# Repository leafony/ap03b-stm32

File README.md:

# Leafony AP03B STM32

**本ボード（AP03B STM32 リーフ）は、AP03 STM32 リーフと回路図が同一で、互換性があります。**

STM32L452REI6を搭載した、Leafony AP03B STM32リーフのハードウェア設計リポジトリです。KiCadの回路図・PCBレイアウト、面付け基板のGerber・ドリルデータ、専用ライブラリ、部品表（BOM）を収録しています。

設計を開く場合は [KiCadプロジェクト](./kicad/ap03b-stm32/ap03b-stm32.kicad_pro)、部品を確認する場合は [BOM](./docs/leafony-ap03b-stm32-bom.csv) から参照してください。

## ハードウェア概要

| 項目 | 内容 |
| --- | --- |
| MCU | STMicroelectronics STM32L452REI6（U1） |
| CPU | Arm Cortex-M4、FPU搭載、最大80 MHz |
| メモリ | Flash 512 KB / SRAM 160 KB |
| MCUパッケージ | UFBGA-64、5 × 5 mm、0.5 mmピッチ |
| 低速外部クロック | 32.768 kHz水晶（X1） |
| 電源 | Leafonyバスの3.3 V / GND |
| バス接点 | CN1、表裏各29接点 |
| 主なバス信号 | D0〜D13、A0〜A5、SDA / SCL、SWDIO / SWCLK、RESET、AREF |
| 操作・表示 | BOOT0切り替えスイッチ、リセットスイッチ、BOOT0状態表示LED |
| 基板 | 20 × 20 mm、6層、板厚0.8 mm（PCB設計値） |
| 設計リビジョン | v1.0、2026-11-07（単体基板・回路図のタイトル欄） |

CPU・メモリの仕様は [STMicroelectronicsの製品情報](https://www.st.com/en/microcontrollers-microprocessors/stm32l452re.html)、実装部品と接続は本リポジトリの回路図・PCB・BOMを参照しています。最大クロックはMCUの仕様値で、実際の動作クロックはファームウェアの設定によります。

CN1のVBUS端子は未接続で、AREFの接続用抵抗R5は未実装（DNP）です。各端子の接続は [Leafonyバス回路図](./kicad/ap03b-stm32/leafony_bus.kicad_sch) と [MCU回路図](./kicad/ap03b-stm32/stm32.kicad_sch) で確認できます。

### スイッチとLED

| 部品 | 型番 | 回路上の役割 |
| --- | --- | --- |
| SW1（PG） | CUS-12TB | BOOT0のHigh / Lowを切り替える |
| SW2（RST） | EVQ-P7B01P | 押すとRESETをGNDへ接続する |
| D1 | SML-A12U8TT86 | BOOT0がHighのときに点灯する |

詳細は [リセット・プログラム切り替え回路](./kicad/ap03b-stm32/reset_prog.kicad_sch) を参照してください。

## リポジトリ構成

| パス | 内容 |
| --- | --- |
| [kicad/ap03b-stm32/ap03b-stm32.kicad_pro](./kicad/ap03b-stm32/ap03b-stm32.kicad_pro) | 単体基板のKiCadプロジェクト |
| [kicad/ap03b-stm32/ap03b-stm32.kicad_sch](./kicad/ap03b-stm32/ap03b-stm32.kicad_sch) | トップレベル回路図。以下の3シートをまとめる |
| [kicad/ap03b-stm32/stm32.kicad_sch](./kicad/ap03b-stm32/stm32.kicad_sch) | MCU、電源、クロック周辺回路 |
| [kicad/ap03b-stm32/leafony_bus.kicad_sch](./kicad/ap03b-stm32/leafony_bus.kicad_sch) | Leafonyバス接点と信号接続 |
| [kicad/ap03b-stm32/reset_prog.kicad_sch](./kicad/ap03b-stm32/reset_prog.kicad_sch) | リセット、BOOT0切り替え、LED、信号切り替え回路 |
| [kicad/ap03b-stm32/ap03b-stm32.kicad_pcb](./kicad/ap03b-stm32/ap03b-stm32.kicad_pcb) | 単体基板のPCBレイアウト |
| [kicad/ap03b-stm32/panelized/](./kicad/ap03b-stm32/panelized/) | 面付け基板のプロジェクト・PCBレイアウト |
| [kicad/ap03b-stm32/panelized/Gerber/](./kicad/ap03b-stm32/panelized/Gerber/) | 面付け基板のGerber・ドリルデータ |
| [kicad/ap03b-stm32/lib/](./kicad/ap03b-stm32/lib/) | Leafony専用シンボル、フットプリント、3Dモデル配置先 |
| [docs/leafony-ap03b-stm32-bom.csv](./docs/leafony-ap03b-stm32-bom.csv) | 部品表（CSV） |
| [examples/](./examples/) | サンプルコード用ディレクトリ。現時点ではコード未収録 |

KiCadプロジェクト名は `ap03b-stm32` で、設計ファイルは `kicad/ap03b-stm32/` にまとめています。

## KiCadで開く

回路図とPCBは **KiCad 10.0** で保存されています。KiCad 10.0形式を読み込める環境と、KiCad標準のシンボル・フットプリントライブラリを用意してください。

1. リポジトリを取得します。

   ```sh
   git clone https://github.com/leafony/ap03b-stm32.git
   cd ap03b-stm32
   ```

2. KiCadで `kicad/ap03b-stm32/ap03b-stm32.kicad_pro` を開きます。
3. プロジェクト内の `.kicad_sch` を開くと回路図、`.kicad_pcb` を開くと基板レイアウトを確認できます。
4. 回路図のトップシートから「STM32 MCU」「Leafony Bus」「Reset Prog」の各階層シートへ移動します。

専用ライブラリは [sym-lib-table](./kicad/ap03b-stm32/sym-lib-table) と [fp-lib-table](./kicad/ap03b-stm32/fp-lib-table) に登録済みです。どちらも `${KIPRJMOD}/lib/` を参照するため、`kicad/ap03b-stm32/` 以下のディレクトリ構成を保って開いてください。

### 面付け基板について

`kicad/ap03b-stm32/panelized/` に面付け基板のプロジェクトとPCB、同ディレクトリの `Gerber/` にGerber・ドリルデータを収録しています。

面付けPCBのタイトル欄は「Leafony AP03 STM32 / 2025-07-06」で、単体基板の「Leafony AP03B STM32 / 2026-11-07」と異なります。製造に使用する場合は、単体基板の変更が面付けPCBとGerber・ドリルデータに反映されているか確認してください。

面付けプロジェクトを開くと `${KIPRJMOD}` の基準は `kicad/ap03b-stm32/panelized/` になります。3Dモデルを表示する場合は、参照先が `kicad/ap03b-stm32/lib/3dmodels/` に解決されるようにモデルパスを調整してください。

## 部品表（BOM）

[BOMのCSV](./docs/leafony-ap03b-stm32-bom.csv) には、部品番号（Reference）、値・型番（Value）、データシート、フットプリント、数量（Qty）、実装対象外の指定（DNP）、メーカー品番（MPN）、メーカー名（MANUFACTURER）を記載しています。

- `R5`、`R7`、`R12`、`R14` はDNP（未実装）です。
- `CN1` はBOMに含まれていません。バス接点の形状・接続は回路図とPCBを参照してください。
- 部品を変更した場合は、回路図と合わせてBOMも更新してください。

## 3Dモデルについて

一部部品の3Dモデルはライセンスの都合上公開できません。`kicad/ap03b-stm32/lib/3dmodels/` にはモデル本体を収録していないため、必要に応じて別途入手し、以下のファイル名で配置してください。Leafony専用の回路図シンボルとフットプリントは同梱しています。

単体基板のPCBが参照するモデルは次のとおりです。

| 部品 | ファイル名（`kicad/ap03b-stm32/lib/3dmodels/` 内） |
| --- | --- |
| U1：STM32L452REI6 | `UFBGA64-5x5mm.step` |
| U2：TS3A4751RUCR | `RUC0014A.stp` |
| SW1：CUS-12TB | `CUS-12TB.step` |
| SW2：EVQ-P7B01P | `EVQP7-KB-01P.STEP` |
| X1：32.768 kHz水晶 | `XTAL_NX2012SA_NDK.step` |
| Q1：RE1C002UNTCL | `DIO_RB558WMF_ROM.step` |
| D1：SML-A12U8TT86 | `SML-A12U8TT86P.stp` |

モデル名は既存のPCB参照に合わせたものです。入手したモデルのパッケージ形状を確認し、PCBエディターの3Dビューアーで位置・向き・縮尺を確認してください。3Dモデルがなくても回路図やPCBレイアウトは確認できます。

単体基板と面付け基板の標準部品のモデルは `${KICAD10_3DMODEL_DIR}` を参照しています。表示されない場合は、KiCadの標準3Dモデルライブラリの導入状況と、この変数の参照先を確認してください。

## ファームウェア・関連資料

このリポジトリには、ファームウェアのビルド設定や書き込みスクリプト、実行可能なサンプルコードは含まれていません。STM32 MCUリーフの開発環境については、Leafony公式資料を参照してください。

- [STM32 MCU スタートガイド](https://docs.leafony.com/getting-started/stm32/)
- [STM32 MCU向けArduino IDEの設定](https://docs.leafony.com/environment/stm32/arduino_ide/)
- [AP03 STM32 MCU 技術資料](https://docs.leafony.com/leaf/processor/ap03/)

AP03B STM32 リーフはAP03 STM32 リーフと回路図が同一で、互換性があるため、開発環境や使い方は上記のAP03向け資料を参照できます。設計ファイルや部品表は、本リポジトリに収録したものを参照してください。

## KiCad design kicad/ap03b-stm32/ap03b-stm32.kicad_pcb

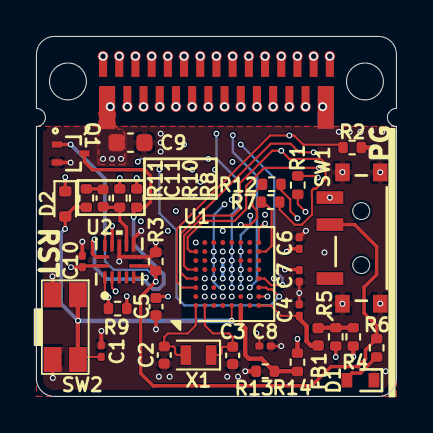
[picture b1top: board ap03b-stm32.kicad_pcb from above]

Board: 6 copper layers, 20.0 x 20.0 mm, 35 parts (0 on the bottom side), 42 nets.

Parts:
C1, C4, C6, C7, C8, C10: 100nF(K)25V; C_0201_0603Metric
C2, C3: 6pF(D)50V; C_0402_1005Metric
C5: 1uF(K)16V; C_0402_1005Metric
C9: 10uF(M)25V; C_0603_1608Metric
C11: 470nF(K)25V; C_0402_1005Metric
CN1: Leafony Bus; CN_F29_B29
D1: SML-A12U8TT86; LED_SML-A12_ROM
D2: 1SS387; D_SOD-523
FB1: MPZ1005S300CT000; Fuse_0402_1005Metric
Q1: RE1C002UNTCL; DIO_RB558WMF_ROM
R1, R2, R3, R8: 10k(J); R_0402_1005Metric
R4, R5, R7, R11, R12, R13, R14: 0R; R_0402_1005Metric
R6: 1k(J); R_0402_1005Metric
R9: 100R(J); R_0402_1005Metric
R10: 100k(J); R_0402_1005Metric
SW1: CUS-12TB; CUS-12TB_NDC
SW2: EVQ-P7B01P
U1: STM32L452REI6; UFBGA-64_5x5mm_Layout8x8_P0.5mm
U2: TS3A4751RUCR; RUC14
X1: NX2012SA-32.768KHZ-EXS00A-MU00530; Crystal_SMD_2012-2Pin_2.0x1.2mm

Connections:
+3V3: C5.1, C6.1, C7.1, C8.1, C9.1, C10.1, CN1.B1 (3.3V), CN1.F1 (3.3V), D2.1 (K), R1.1, R2.1, R4.2, R8.1, R10.1, SW1.3, U1.B2 (VBAT), U1.D2 (VDD), U1.E4 (VDD), U1.E5 (VDDUSB), U1.E6 (VDD), U2.14 (V+)
A0: CN1.B6 (A0), CN1.F6 (A0), U1.H3 (PA4)
A1: CN1.B8 (A1), CN1.F8 (A1), U1.G2 (PA0)
A2: CN1.B10 (A2), CN1.F10 (A2), U1.H2 (PA1)
A3: CN1.B12 (A3), CN1.F12 (A3), R14.2, U1.F5 (PB0)
A4: CN1.B14 (A4), CN1.F14 (A4), U1.E2 (PC1)
A5: CN1.B16 (A5), CN1.F16 (A5), U1.E3 (PC0)
AREF: CN1.B4 (AREF), CN1.F4 (AREF), R5.2
BOOT0: Q1.1, R3.1, R6.1, SW1.2, U1.B4 (PH3), U2.6 (IN3), U2.12 (IN4)
D0: CN1.B18 (D0), CN1.F18 (D0), U1.G3 (PA3)
D1: CN1.B20 (D1), CN1.F20 (D1), U1.F3 (PA2)
D2: CN1.B22 (D2), CN1.F22 (D2), U1.E7 (PC7)
D3: CN1.B24 (D3), CN1.F24 (D3), R7.2, U1.A5 (PB3)
D4: CN1.B26 (D4), CN1.F26 (D4), R12.2, U1.C4 (PB5)
D5: CN1.B28 (D5), CN1.F28 (D5), U1.A4 (PB4)
D6: CN1.B7 (D6), CN1.F7 (D6), U1.D7 (PA8)
D7: CN1.B9 (D7), CN1.F9 (D7), U1.H8 (PB12)
D8: CN1.B11 (D8), CN1.F11 (D8), U1.C7 (PA9)
D9: CN1.B13 (D9), CN1.F13 (D9), U2.2 (COM1)
D10: CN1.B15 (D10), CN1.F15 (D10), U1.D3 (PB6)
D11: CN1.B17 (D11), CN1.F17 (D11), U1.H4 (PA7)
D12: CN1.B19 (D12), CN1.F19 (D12), U1.G4 (PA6)
D13: CN1.B21 (D13), CN1.F21 (D13), U1.F4 (PA5)
GND: C1.2, C2.2, C3.2, C4.2, C5.2, C6.2, C7.2, C8.2, C9.2, C10.2, CN1.B27 (GND), CN1.F27 (GND), D1.1 (K), Q1.2, R3.2, R13.1, SW1.SH, SW2.2, SW2.3, U1.C2 (VSS), U1.D4 (VSS), U1.D5 (VSS), U1.D6 (VSS), U2.7 (GND), U2.8 (NO3), U2.10 (COM4)
unnamed: C11.2, R11.1
unnamed: D1.2 (A), R6.2
unnamed: FB1.2, R4.1, R5.1
unnamed: R7.1, U1.H7 (PB11)
unnamed: R12.1, U1.F7 (PB15)
unnamed: C2.1, U1.A1 (PC14), X1.2
unnamed: C3.1, U1.B1 (PC15), X1.1
unnamed: C4.1, FB1.1, U1.H1 (VDDA)
unnamed: R13.2, R14.1, U1.F1 (VSSA)
unnamed: C11.1, R10.2, U2.9 (COM3)
unnamed: Q1.3, R8.2, U2.5 (IN2), U2.13 (IN1)
unnamed: R9.2, U2.11 (NO4)
PA10: R9.1, U1.C6 (PA10), U2.1 (NO1)
RESET: C1.1, CN1.B5 (RESET), CN1.F5 (RESET), D2.2 (A), R11.2, SW2.1, SW2.4, U1.E1 (NRST)
SCL: CN1.B25 (SCL), CN1.F25 (SCL), R1.2, U1.B3 (PB8)
SDA: CN1.B23 (SDA), CN1.F23 (SDA), R2.2, U1.A3 (PB9)
SWCLK: CN1.B29 (SWCLK), CN1.F29 (SWCLK), U1.A7 (PA14)
SWDIO: CN1.B2 (SWDIO), CN1.F2 (SWDIO), U1.A8 (PA13)

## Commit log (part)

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2026-04-27 回路図・レイアウトを追加
2026-04-27 BOMを追加
2026-04-27 BOMからCN1を除外
